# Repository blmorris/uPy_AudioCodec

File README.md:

# uPy_AudioCodec

The uPy_AudioCodec is a daughterboard for the [MicroPython pyboard](http://micropython.org)
containing:
* The SSM2604 I2S audio codec chip from Analog Devices: [Webpage](http://www.analog.com/en/products/audio-video/audio-amplifiers/ssm2604.html), [Datasheet](http://www.analog.com/media/en/technical-documentation/data-sheets/SSM2604.pdf)
* The TPA6130A2 headphone amplifer from Texas Instruments: [Webpage](http://www.ti.com/product/TPA6130A2), [Datasheet](http://www.ti.com/lit/ds/symlink/tpa6130a2.pdf)

This repository contains the design files for the board along with
code to use it with MicroPython.

# Quick Start

To use the uPy_AudioCodec you will need the following:
* A MicroPython pyboard
* The codec board along with the optional microphone plug
* A 16-bit stereo *.wav file encoded at either 44.1kHz (CD-quality) or 48kHz
  sample rate. (Other sample rates are theoretically supported but
  untested so far.)

* A micro-SD card (to store the *.wav file)
* A pair of headphones or earbuds with 3.5mm (1/8") stereo plug

Assemble the daughterboard in the pyboard with the microphone plug and
headphone plugged in as shown in the picture. Note that the
daughterboard must occupy the 'Y' position in the pyboard, as the SPI
port in the 'X' position (SPI1) does not support I2S.

Use DFU to load I2S supporting uPy firmware to pyboard:
[prebuilt firmware image in firmware/i2s-firmware.dfu](firmware/i2s-firmware.dfu)

Until I2S support is merged into master at http://github.com/micropython/micropython I will occasionally update the I2S firmware image to track my [micropython i2s branch](https://github.com/blmorris/micropython/tree/i2s)

The following code is a very quick-and-dirty way to initialize the
AudioCodec board in python - I will clean this up soon!:

```Python
import pyb
pot = pyb.ADC('Y12')
hpctl = pyb.Pin('Y11')
hpctl.init(hpctl.OUT_PP)
hpctl.high()
i2c = pyb.I2C(2)
i2c.init(i2c.MASTER)
# Might do a 'try' here to make sure both i2c devices are working:
i2c.scan()
# Should give [26, 96]

# Set Headphone Amp chip registers:
i2c.mem_write(0xc0, 96, 1) # control register: enable both amplifier channels, activate stereo mode
i2c.mem_write(0x35, 96, 2) # volume register; unmute both channels, set gain to ~0dB
i2c.mem_write(0x00, 96, 3) # output tri-state register; set both channels to output mode

# Set codec registers:
# THe SSM2604 uses a register addressing scheme that does not map directly to the uPy
# mem_read / mem_write methods.
# There are a total of 11 9-bit registers (R0-R9 and R15) which are selected using a
# 7-bit address. Register writes are constructed using the 'send' method:
# i2c.send('0b<7-bit register address><9-bit register data>', 26)
# Register reads can use 'mem_read' but the register address must be multiplied by 2
# (or shifted 1 bit left, so the 7-bit address is left justified)
# The read should be for two bytes, and the 'bytes' object that is returned will be
# two bytes long with the LSB first

# Set up Codec for Pass-Through
i2c.send(b'\x00\x17', 26) # LEFT ADC INPUT GAIN, ADDRESS 0x00: unmute left ADC, input gain=0dB
i2c.send(b'\x02\x17', 26) # RIGHT ADC INPUT GAIN, ADDRESS 0x01: unmute right ADC, input gain=0dB
# R2 and R3 are reserved
i2c.send(b'\x08\x08', 26) # ANALOG AUDIO PATH, ADDRESS 0x04: Bypass select, DAC not selected
i2c.send(b'\x0a\x08', 26) # DIGITAL AUDIO PATH, ADDRESS 0x05: leave default, DAC is muted
i2c.send(b'\x0c\x7e', 26) # POWER MANAGEMENT, ADDRESS 0x06: power on chip and line-in
#i2c.send(b'\x0e\x0a', 26) # DIGITAL AUDIO I/F, ADDRESS 0x07: I2S parameters, leave default
i2c.send(b'\x0e\x02', 26) # DIGITAL AUDIO I/F, ADDRESS 0x07: Set 16-bit, I2S mode
i2c.send(b'\x10\x00', 26) # SAMPLING RATE, ADDRESS 0x08: leave default

# Set up Codec for DAC playback:
i2c.send(b'\x08\x10', 26)
i2c.send(b'\x0a\x00', 26)
i2c.send(b'\x0c\x72', 26)
i2c.send(b'\x0e\x02', 26)
i2c.send(b'\x10\x00', 26)
i2c.send(b'\x12\x01', 26)

tim = pyb.Timer(1, freq=20)
def set_volume(tim, buf=bytearray(1)):
    buf[0] = pot.read() >> 6
    i2c.mem_write(buf, 96, 2)

tim.callback(set_volume)

i2s = pyb.I2S()
i2s.init(i2s.MASTER, mclkout=1)
i2s.stream_out(f)

def test_stream():
    i2c.send(b'\x00\x17', 26) # LEFT IN GAIN = 0dB
    i2c.send(b'\x02\x17', 26) # RIGHT IN GAIN = 0dB
    i2c.send(b'\x08\x10', 26)

def test_mic():
    i2c.send(b'\x00\x27', 26) # LEFT IN GAIN = +24dB
    i2c.send(b'\x02\x27', 26) # RIGHT IN GAIN = +24dB
    i2c.send(b'\x08\x08', 26)

```

Then the following to start streaming out to your headphones:

```Python
f = open('/path/to/wave/file', 'rb')
f.seek(44) # to skip past wave file header
i2s.stream_out(f)
```

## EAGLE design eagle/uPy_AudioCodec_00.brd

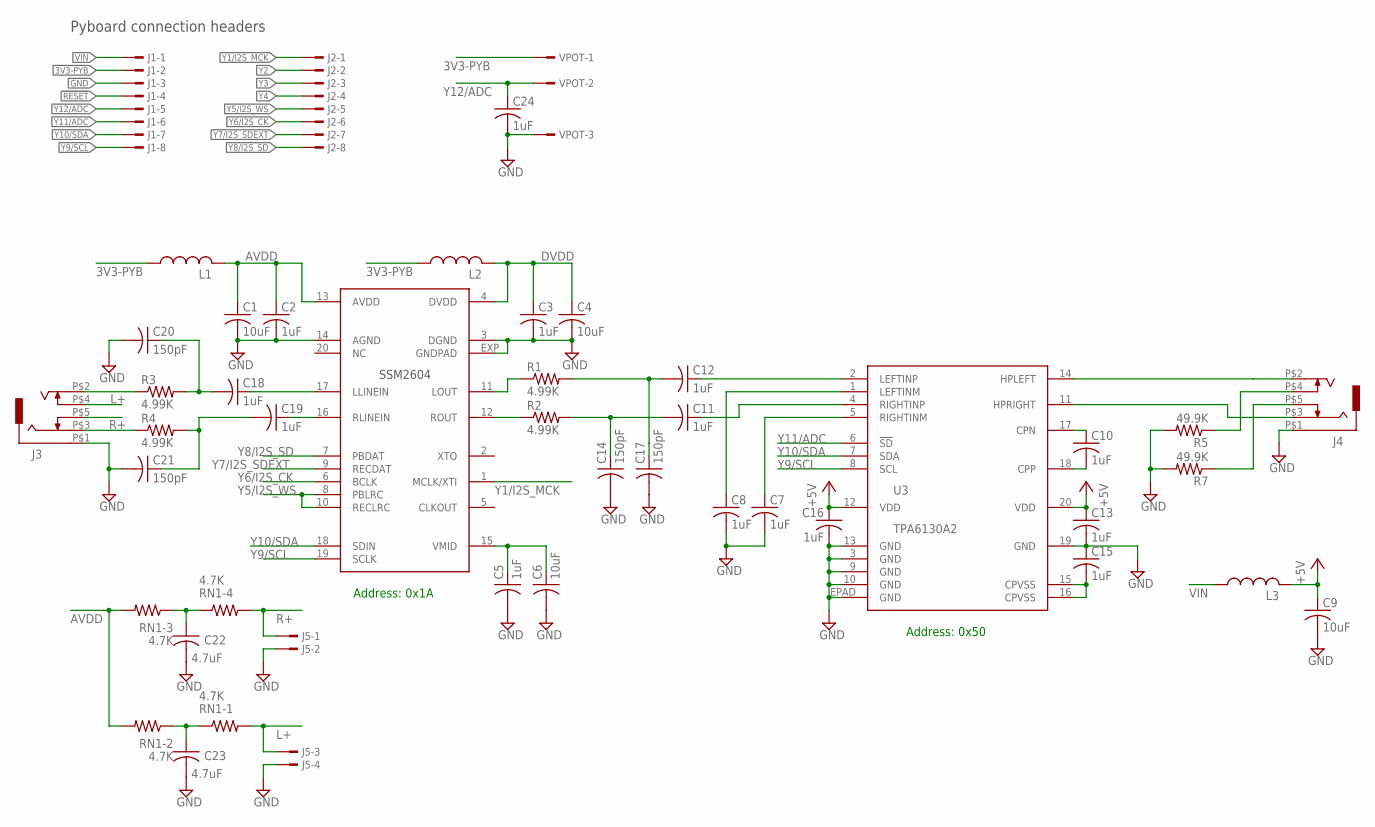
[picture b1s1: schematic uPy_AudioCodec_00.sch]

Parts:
C1: 10uF; C0603K
C2: 1uF; C0805K
C3, C5, C7, C8, C10, C11, C12, C13, C15, C16, C18, C19, C24: 1uF; C0603K
C4, C6, C9: 10uF; C0805K
C14, C17, C20, C21: 150pF; C0603K
C22, C23: 4.7uF; C0603K
J1, J2: TSW-108-02-S-S-MOD
J3, J4: CON-JACK-STEREO; CON-JACK-SJ1-3515-SMT
J5: TSW-104-02-S-S; TSW-104-02-S-S-MOD
L1, L2, L3: L-USL3216C; L3216C
R1, R2, R3, R4: 4.99K; R0805
R5, R7: 49.9K; R0805
RN1: 4.7K; CTS-742C083+
U1: SSM2604-1; LFCSP20-1
U3: TPA6130A2; QFN20-EP
VPOT: TSW-103-02-S-S; TSW-103-02-S-S-MOD

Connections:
3V3-PYB: J1.2, L1.1, L2.1, VPOT.1
!RESET: J1.4
+5V: C9.1, C13.1, C16.1, L3.2, U3.12 (VDD), U3.20 (VDD)
AVDD: C1.1, C2.1, L1.2, RN1.P$6 (2), RN1.P$7 (2), U1.13 (AVDD)
DVDD: C3.1, C4.1, L2.2, U1.4 (DVDD)
GND: C1.2, C2.2, C3.2, C4.2, C5.2, C6.2, C7.2, C8.2, C9.2, C13.2, C14.2, C15.1, C16.2, C17.2, C20.2, C21.2, C22.2, C23.2, C24.2, J1.3, J3.P$1 (SLEEVE), J4.P$1 (SLEEVE), J5.2, J5.4, R5.2, R7.2, U1.3 (DGND), U1.14 (AGND), U1.EXP (GNDPAD), U3.3 (GND), U3.9 (GND), U3.10 (GND), U3.13 (GND), U3.19 (GND), U3.EPAD (GND), VPOT.3
L+: J3.P$4 (TIP_SW), J5.3, RN1.P$8 (2)
unnamed: C12.1, U3.2 (LEFTINP)
unnamed: C18.1, U1.17 (LLINEIN)
unnamed: C19.1, U1.16 (RLINEIN)
unnamed: C11.1, U3.4 (RIGHTINP)
unnamed: J4.P$2 (TIP), U3.14 (HPLEFT)
unnamed: C5.1, C6.1, U1.15 (VMID)
unnamed: C7.1, U3.5 (RIGHTINM)
unnamed: C8.1, U3.1 (LEFTINM)
unnamed: R1.1, U1.11 (LOUT)
unnamed: C15.2, U3.15 (CPVSS), U3.16 (CPVSS)
unnamed: C10.2, U3.18 (CPP)
unnamed: J4.P$3 (RING), U3.11 (HPRIGHT)
unnamed: C10.1, U3.17 (CPN)
unnamed: R2.1, U1.12 (ROUT)
unnamed: C11.2, C14.1, R2.2
unnamed: J4.P$5 (RING_SW), R7.1
unnamed: J4.P$4 (TIP_SW), R5.1
unnamed: C12.2, C17.1, R1.2
unnamed: J3.P$3 (RING), R4.1
unnamed: J3.P$2 (TIP), R3.1
unnamed: C18.2, C20.1, R3.2
unnamed: C19.2, C21.1, R4.2
unnamed: C22.1, RN1.P$3 (1), RN1.P$4 (1)
unnamed: C23.1, RN1.P$1 (1), RN1.P$2 (1)
R+: J3.P$5 (RING_SW), J5.1, RN1.P$5 (2)
VIN: J1.1, L3.1
Y1/I2S_MCK: J2.1, U1.1 (MCLK/XTI)
Y2: J2.2
Y3: J2.3
Y4: J2.4
Y5/I2S_WS: J2.5, U1.8 (PBLRC), U1.10 (RECLRC)
Y6/I2S_CK: J2.6, U1.6 (BCLK)
Y7/I2S_SDEXT: J2.7, U1.9 (RECDAT)
Y8/I2S_SD: J2.8, U1.7 (PBDAT)
Y9/SCL: J1.8, U1.19 (SCLK), U3.8 (SCL)
Y10/SDA: J1.7, U1.18 (SDIN), U3.7 (SDA)
Y11/ADC: J1.6, U3.6 (!SD)
Y12/ADC: C24.1, J1.5, VPOT.2

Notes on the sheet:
Pyboard connection headers
Address: 0x50
SSM2604
Address: 0x1A

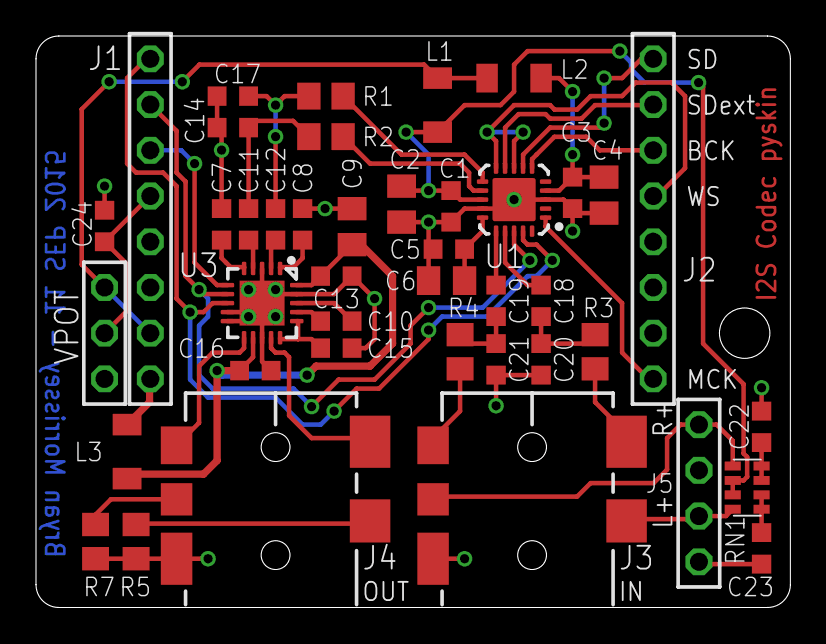
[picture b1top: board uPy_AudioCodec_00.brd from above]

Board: 2 copper layers, 41.9 x 31.8 mm, 42 parts (0 on the bottom side), 41 nets.

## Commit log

2015-09-11 Initial commit of uPy_AudioCodec Eagle project files
2015-09-11 Remove superfluous PDF file from repo
2015-10-16 README.md: Begin quickstart instructions
2015-10-16 README.md: more instructions
2015-10-28 Add some reference links to README.md
2015-10-28 Remove unnecessary parens
2015-10-28 Directory reorganization: eagle files moved to eagle/, pdf files moved to docs/, add gerber files
2015-10-28 firmware: Add firmware supporting stream_in and stream_out functions
2015-11-14 firmware: Update i2s-firmware.dfu to latest build
2015-12-02 src: Add boot.py and codec.py source files and copy of current (broken) firmware: i2s-firmware_NW.dfu
